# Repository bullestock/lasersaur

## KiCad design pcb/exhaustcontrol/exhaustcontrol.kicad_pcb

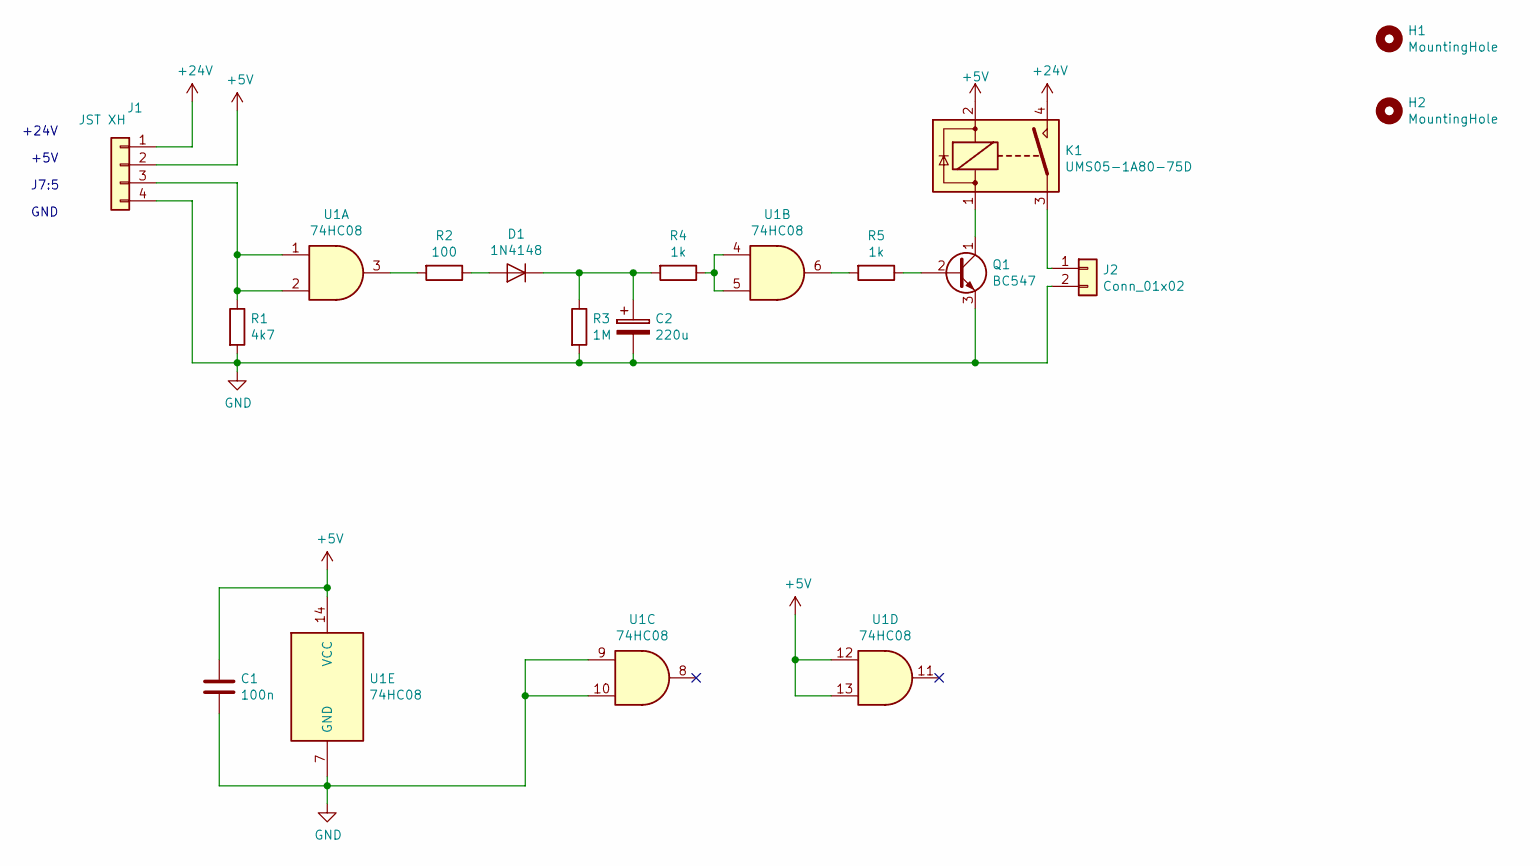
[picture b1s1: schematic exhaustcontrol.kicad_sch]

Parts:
C1: 100n; C_Axial_L5.1mm_D3.1mm_P10.00mm_Horizontal
C2: 220u; CP_Radial_D10.0mm_P2.50mm_P5.00mm
D1: 1N4148; D_DO-35_SOD27_P7.62mm_Horizontal
H1, H2: MountingHole; MountingHole_3.2mm_M3
J1: JST XH; JST_XH_B04B-XH-A_1x04_P2.50mm_Vertical
J2: Conn_01x02; JST_XH_B02B-XH-A_1x02_P2.50mm_Vertical
K1: UMS05-1A80-75D; DIL-relay
Q1: BC547; TO-92_Wide
R1: 4k7; R_Axial_DIN0411_L9.9mm_D3.6mm_P12.70mm_Horizontal
R2: 100; R_Axial_DIN0411_L9.9mm_D3.6mm_P12.70mm_Horizontal
R3: 1M; R_Axial_DIN0411_L9.9mm_D3.6mm_P12.70mm_Horizontal
R4, R5: 1k; R_Axial_DIN0411_L9.9mm_D3.6mm_P12.70mm_Horizontal
U1: 74HC08; DIP-14_W7.62mm_LongPads

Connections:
+5V: C1.1, J1.2, K1.2, U1.12, U1.13, U1.14 (VCC)
+24V: J1.1, K1.4
GND: C1.2, C2.2, J1.4, J2.2, Q1.3 (E), R1.2, R3.2, U1.7 (GND), U1.9, U1.10
unnamed: C2.1, D1.1 (K), R3.1, R4.2
unnamed: D1.2 (A), R2.1
unnamed: J1.3, R1.1, U1.1, U1.2
unnamed: J2.1, K1.3
unnamed: K1.1, Q1.1 (C)
unnamed: Q1.2 (B), R5.1
unnamed: R2.2, U1.3
unnamed: R4.1, U1.4, U1.5
unnamed: R5.2, U1.6

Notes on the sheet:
+24V
+5V
J7:5
GND

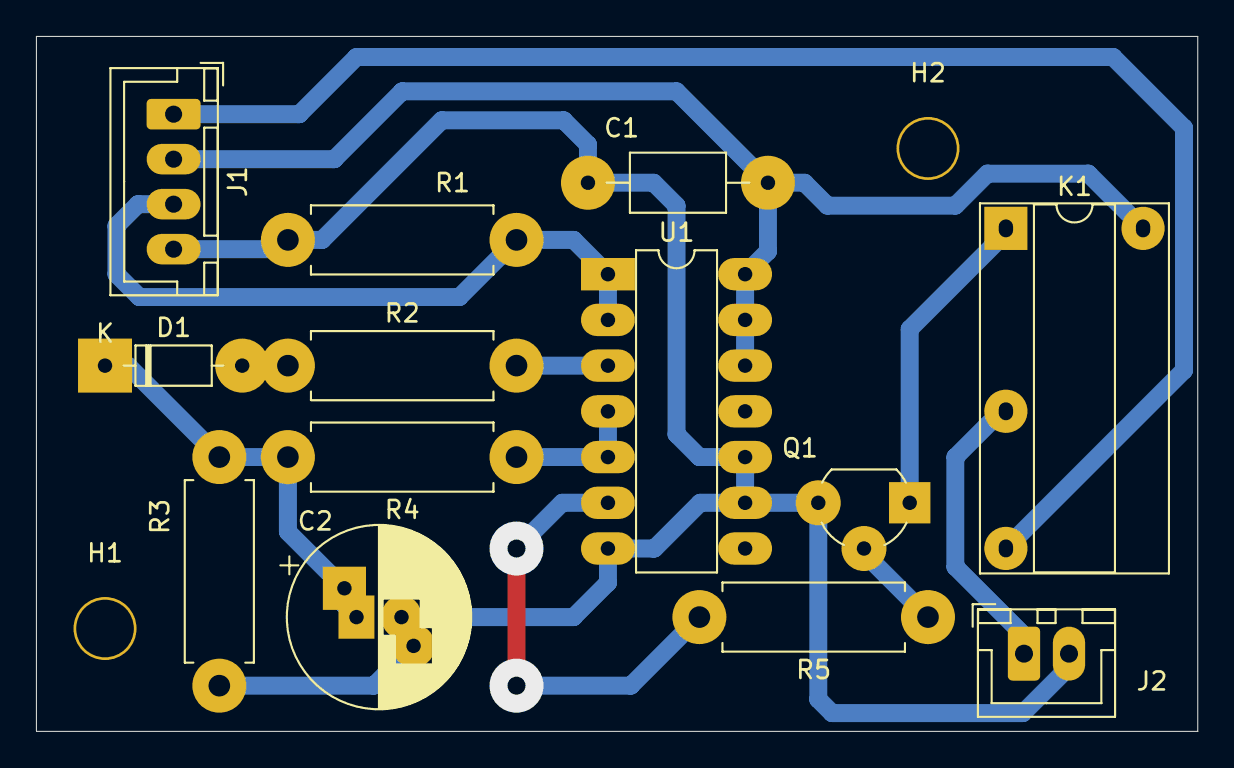
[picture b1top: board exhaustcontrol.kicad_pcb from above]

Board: 2 copper layers, 64.5 x 38.6 mm, 15 parts (0 on the bottom side), 12 nets.

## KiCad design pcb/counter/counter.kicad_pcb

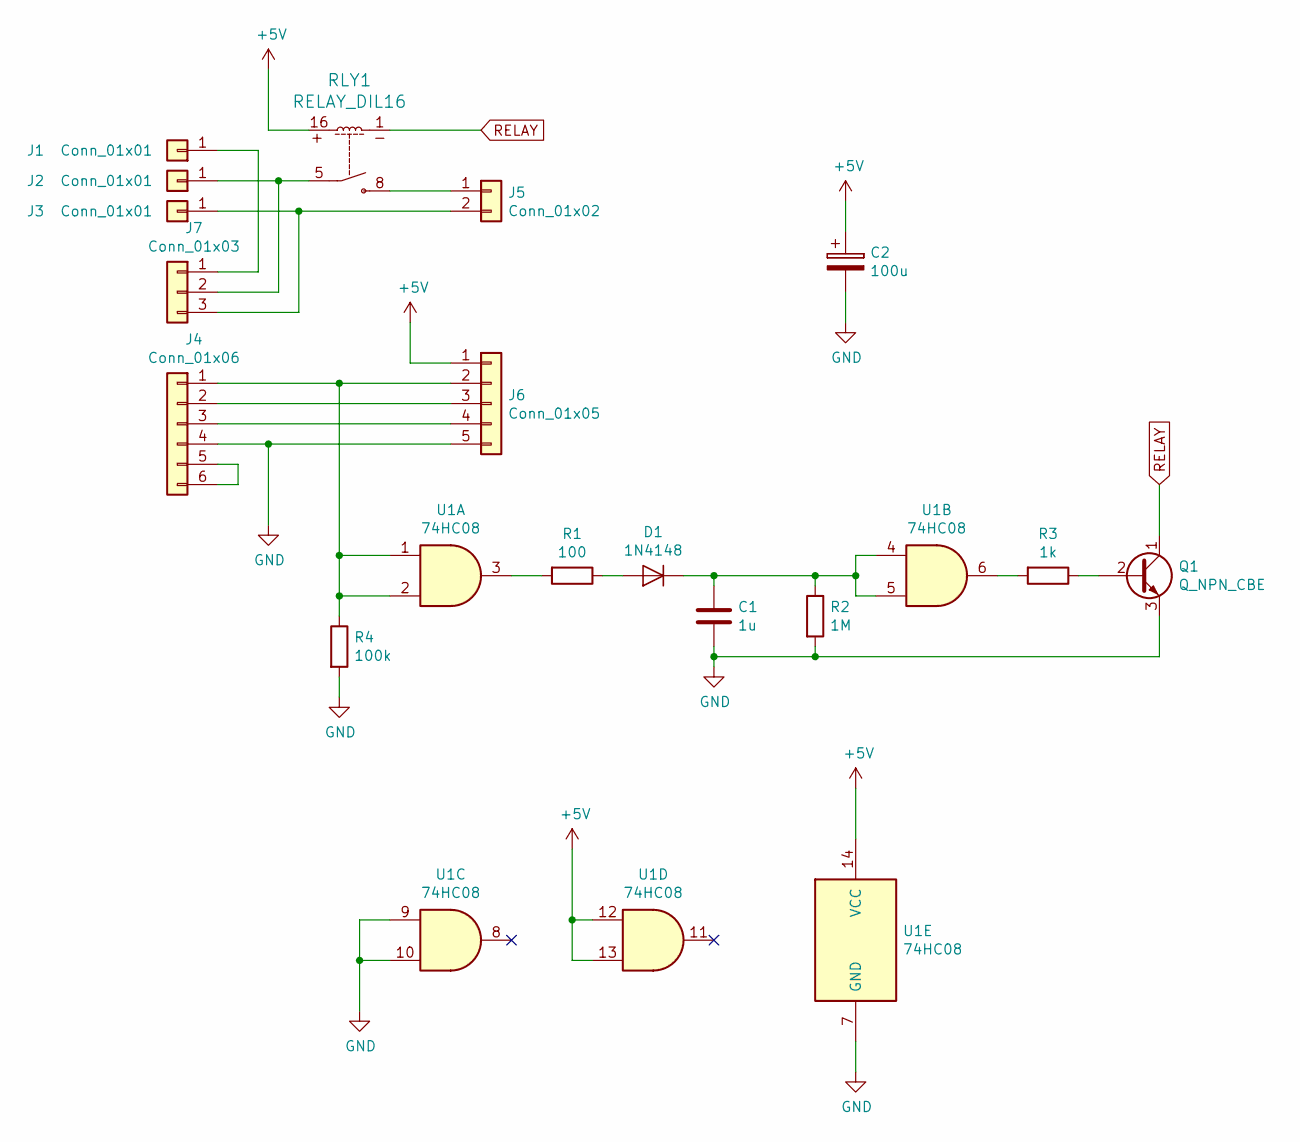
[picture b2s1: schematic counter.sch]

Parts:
C1: 1u; C_Rect_L11.0mm_W7.3mm_P10.00mm_MKT
C2: 100u; CP_Radial_D10.0mm_P2.50mm_P5.00mm
D1: 1N4148; D_DO-41_SOD81_P10.16mm_Horizontal
J1, J2, J3: Conn_01x01; Pin_D1.0mm_L10.0mm
J4: Conn_01x06; TerminalBlock_bornier-6_P5.08mm
J5: Conn_01x02; TerminalBlock_bornier-2_P5.08mm
J6: Conn_01x05; JST_XH_B05B-XH-A_1x05_P2.50mm_Vertical
J7: Conn_01x03; TerminalBlock_Altech_AK300-3_P5.00mm
Q1: Q_NPN_CBE; TO-92L_Wide
R1: 100; R_Axial_DIN0411_L9.9mm_D3.6mm_P12.70mm_Horizontal
R2: 1M; R_Axial_DIN0411_L9.9mm_D3.6mm_P5.08mm_Vertical
R3: 1k; R_Axial_DIN0411_L9.9mm_D3.6mm_P12.70mm_Horizontal
R4: 100k; R_Axial_DIN0411_L9.9mm_D3.6mm_P7.62mm_Vertical
RLY1: RELAY_DIL16; DIP-16_Relay
U1: 74HC08; DIP-14_W7.62mm_LongPads

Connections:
+5V: C2.1, J6.1, RLY1.16, U1.12, U1.13, U1.14 (VCC)
GND: C1.2, C2.2, J4.4, J6.5, Q1.3 (E), R2.2, R4.2, U1.7 (GND), U1.9, U1.10
unnamed: C1.1, D1.1 (K), R2.1, U1.4, U1.5
unnamed: D1.2 (A), R1.1
unnamed: J1.1, J7.1
unnamed: J2.1, J7.2, RLY1.5
unnamed: J3.1, J5.2, J7.3
unnamed: J4.1, J6.2, R4.1, U1.1, U1.2
unnamed: J4.2, J6.3
unnamed: J4.3, J6.4
unnamed: J4.5, J4.6
unnamed: J5.1, RLY1.8
unnamed: Q1.2 (B), R3.1
unnamed: R1.2, U1.3
unnamed: R3.2, U1.6
RELAY: Q1.1 (C), RLY1.1

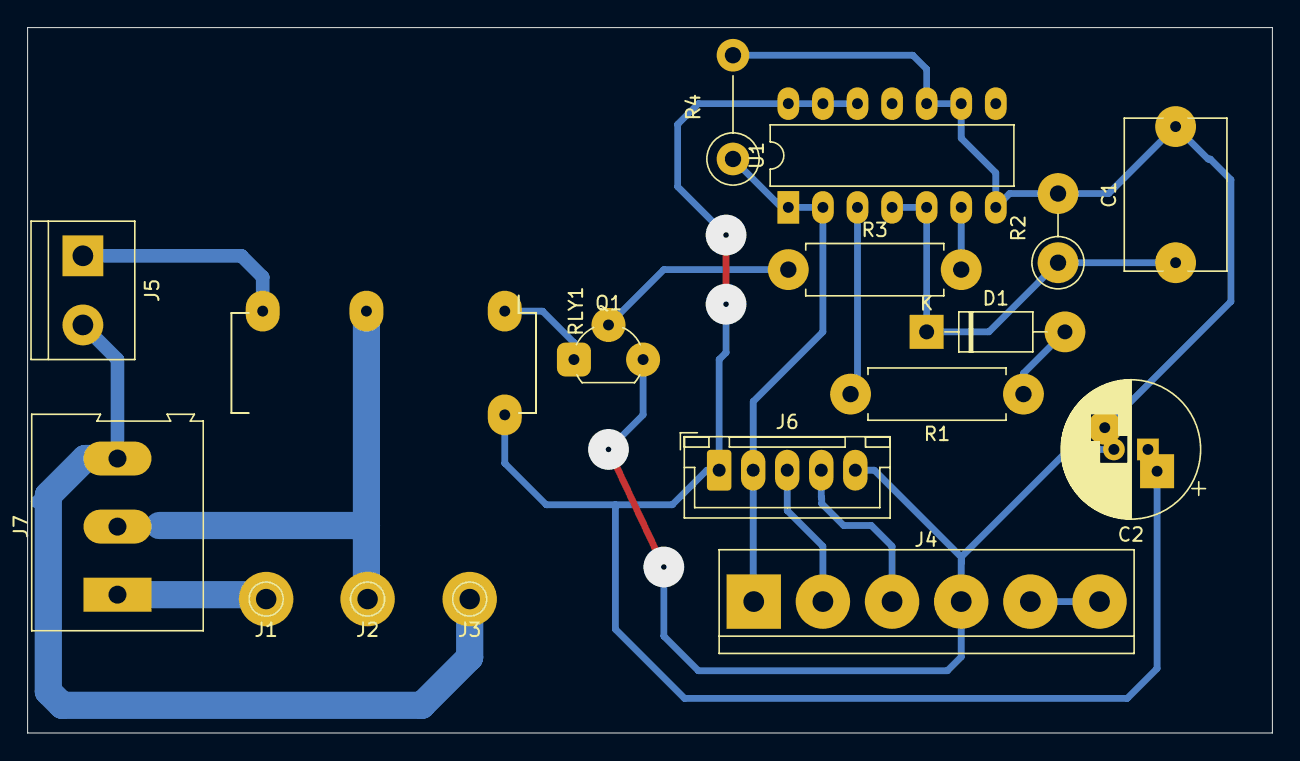
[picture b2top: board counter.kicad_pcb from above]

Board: 2 copper layers, 91.4 x 51.8 mm, 17 parts (0 on the bottom side), 16 nets.

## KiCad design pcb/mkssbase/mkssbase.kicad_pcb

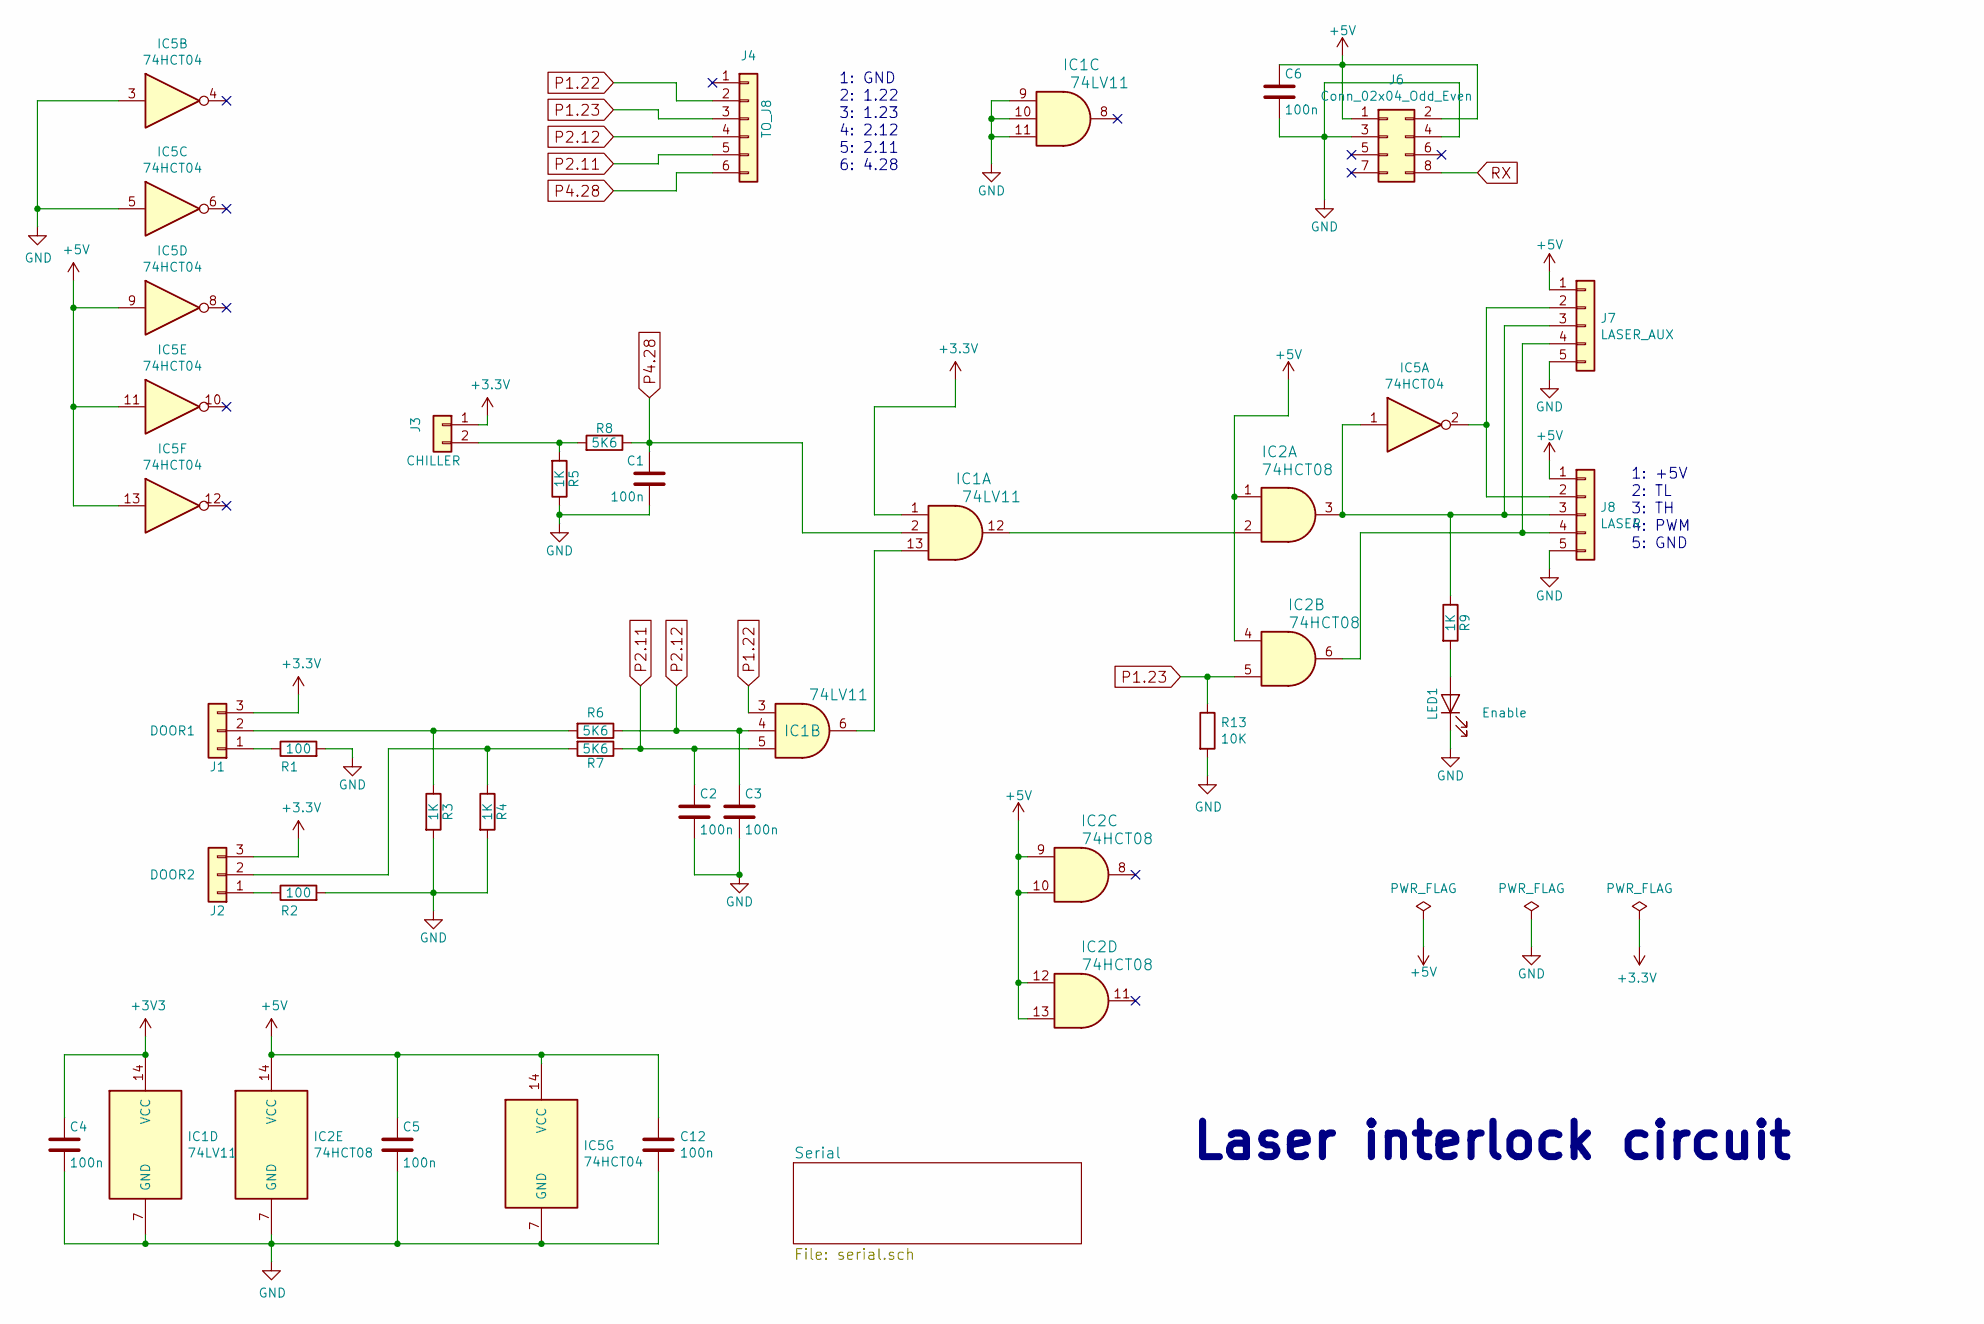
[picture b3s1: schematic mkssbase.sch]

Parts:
C1, C2, C3, C4, C5, C6, C12: 100n; C_0603_1608Metric
IC1: 74LV11; SOIC-14_3.9x8.7mm_P1.27mm
IC2: 74HCT08; SOIC-14_3.9x8.7mm_P1.27mm
IC5: 74HCT04; SOIC-14_3.9x8.7mm_P1.27mm
J1: DOOR1; JST_PH_B3B-PH-K_1x03_P2.00mm_Vertical
J2: DOOR2; JST_PH_B3B-PH-K_1x03_P2.00mm_Vertical
J3: CHILLER; JST_PH_B2B-PH-K_1x02_P2.00mm_Vertical
J4: TO_J8; JST_XH_B06B-XH-A_1x06_P2.50mm_Vertical
J6: Conn_02x04_Odd_Even; PinSocket_2x04_P2.54mm_Vertical
J7: LASER_AUX; JST_PH_B5B-PH-K_1x05_P2.00mm_Vertical
J8: LASER; JST_PH_B5B-PH-K_1x05_P2.00mm_Vertical
LED1: Enable; LED_0603_1608Metric
R1, R2: 100; R_0603_1608Metric
R3, R4, R5, R9: 1K; R_0603_1608Metric
R6, R7, R8: 5K6; R_0603_1608Metric
R13: 10K; R_0603_1608Metric

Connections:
+5V: C5.1, C6.1, C12.1, IC2.1, IC2.4, IC2.9, IC2.10, IC2.12, IC2.13, IC2.14 (VCC), IC5.9, IC5.11, IC5.13, IC5.14 (VCC), J6.1, J6.2, J7.1, J8.1; also elsewhere on the board
GND: C1.2, C2.2, C3.2, C4.2, C5.2, C6.2, C12.2, IC1.7 (GND), IC1.9, IC1.10, IC1.11, IC2.7 (GND), IC5.3, IC5.5, IC5.7 (GND), J6.3, J6.4, J7.5, J8.5, LED1.1 (K), R1.2, R2.2, R3.2, R4.2, R5.1, R13.2; also elsewhere on the board
unnamed: IC1.12, IC2.2
unnamed: IC1.6, IC1.13
unnamed: IC2.3, IC5.1, J7.3, J8.3, R9.1
unnamed: IC2.6, J7.4, J8.4
unnamed: IC5.2, J7.2, J8.2
unnamed: J1.1, R1.1
unnamed: J1.2, R3.1, R6.2
unnamed: J2.1, R2.1
unnamed: J2.2, R4.1, R7.2
unnamed: J3.2, R5.2, R8.2
unnamed: LED1.2 (A), R9.2
P1.22: IC1.3, J4.2
P1.23: IC2.5, J4.3, R13.1
P2.11: C2.1, IC1.5, J4.5, R7.1
P2.12: C3.1, IC1.4, J4.4, R6.1
P4.28: C1.1, IC1.2, J4.6, R8.1
RX: J6.8; also elsewhere on the board

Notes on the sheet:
1: +5V 2: TL 3: TH 4: PWM 5: GND
Laser interlock circuit
1: GND 2: 1.22 3: 1.23 4: 2.12 5: 2.11 6: 4.28

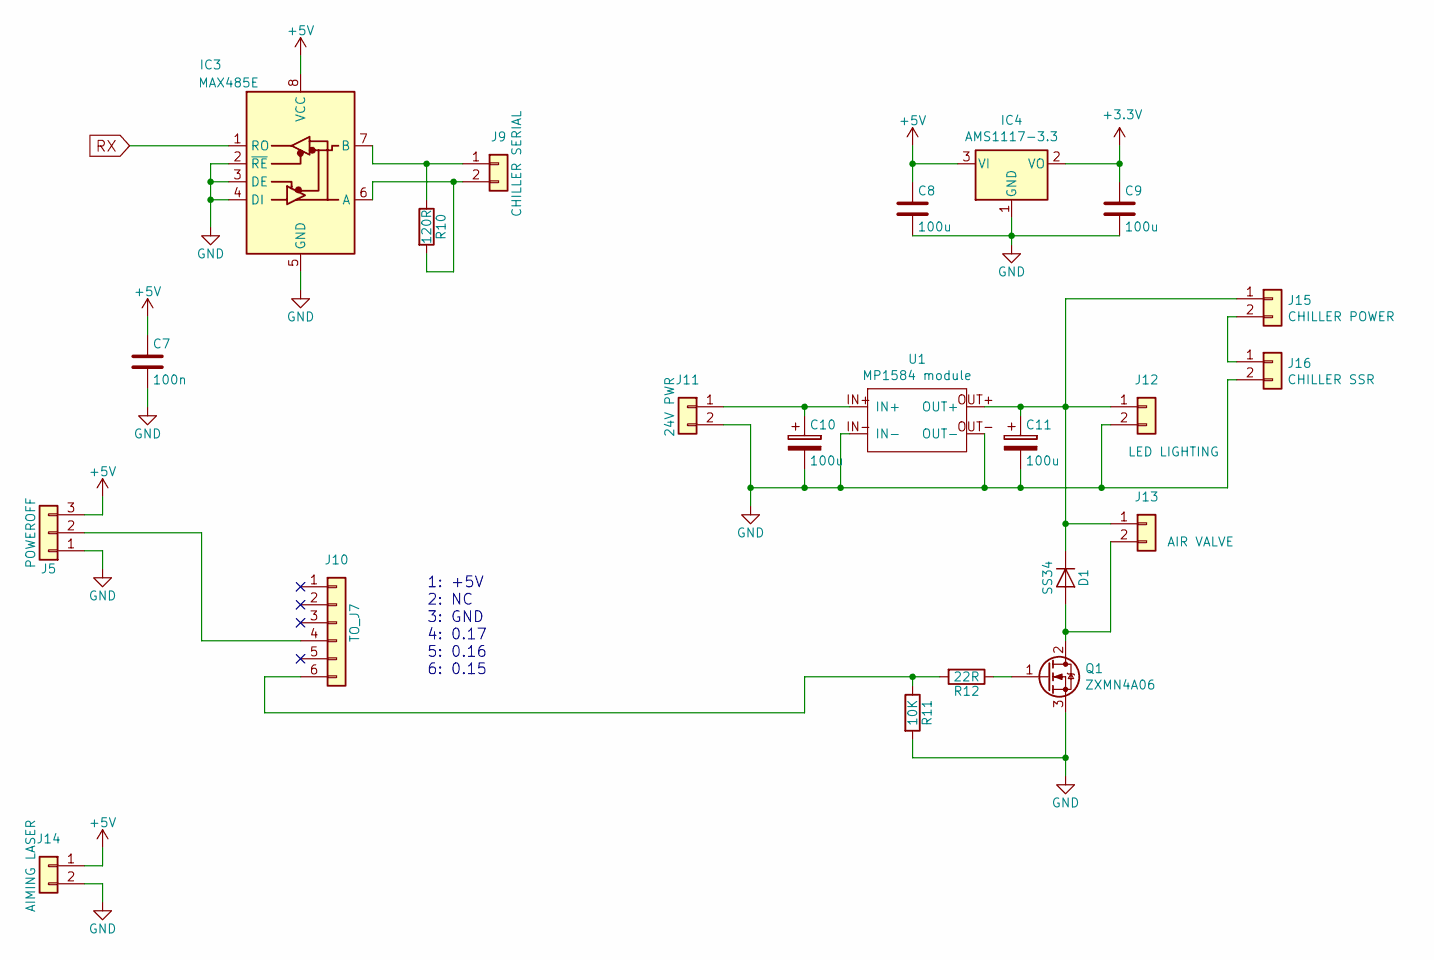
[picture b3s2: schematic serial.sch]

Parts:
C7: 100n; C_0603_1608Metric
C8, C9, C10, C11: 100u; CP_Elec_10x10
D1: SS34; D_SMA
IC3: MAX485E; SOIC-8_3.9x4.9mm_P1.27mm
IC4: AMS1117-3.3; SOT-223-3_TabPin2
J5: POWEROFF; JST_PH_B3B-PH-K_1x03_P2.00mm_Vertical
J9: CHILLER SERIAL; JST_PH_B2B-PH-K_1x02_P2.00mm_Vertical
J10: TO_J7; JST_XH_B06B-XH-A_1x06_P2.50mm_Vertical
J11: 24V PWR; JST_PH_B2B-PH-K_1x02_P2.00mm_Vertical
J12: LED LIGHTING; JST_PH_B2B-PH-K_1x02_P2.00mm_Vertical
J13: AIR VALVE; JST_PH_B2B-PH-K_1x02_P2.00mm_Vertical
J14: AIMING LASER; JST_PH_B2B-PH-K_1x02_P2.00mm_Vertical
J15: CHILLER POWER; JST_PH_B2B-PH-K_1x02_P2.00mm_Vertical
J16: CHILLER SSR; JST_PH_B2B-PH-K_1x02_P2.00mm_Vertical
Q1: ZXMN4A06; SOT-223-3_TabPin2
R10: 120R; R_0603_1608Metric
R11: 10K; R_0603_1608Metric
R12: 22R; R_0603_1608Metric
U1: MP1584 module; MP1584-module

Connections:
+5V: C7.1, C8.1, IC3.8 (VCC), IC4.3 (VI), J5.3, J14.1; also elsewhere on the board
GND: C7.2, C8.2, C9.2, C10.2, C11.2, IC3.2 (~RE), IC3.3 (DE), IC3.4 (DI), IC3.5 (GND), IC4.1 (GND), J5.1, J11.2, J12.2, J14.2, J16.2, Q1.3 (S), R11.2, U1.IN-, U1.OUT-; also elsewhere on the board
unnamed: C10.1, J11.1, U1.IN+
unnamed: C11.1, D1.1 (K), J12.1, J13.1, J15.1, U1.OUT+
unnamed: D1.2 (A), J13.2, Q1.2 (D)
unnamed: IC3.6 (A), J9.2, R10.2
unnamed: IC3.7 (B), J9.1, R10.1
unnamed: J5.2, J10.4
unnamed: J10.6, R11.1, R12.2
unnamed: J15.2, J16.1
unnamed: Q1.1 (G), R12.1
RX: IC3.1 (RO); also elsewhere on the board

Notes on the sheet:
1: +5V 2: NC 3: GND 4: 0.17 5: 0.16 6: 0.15

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
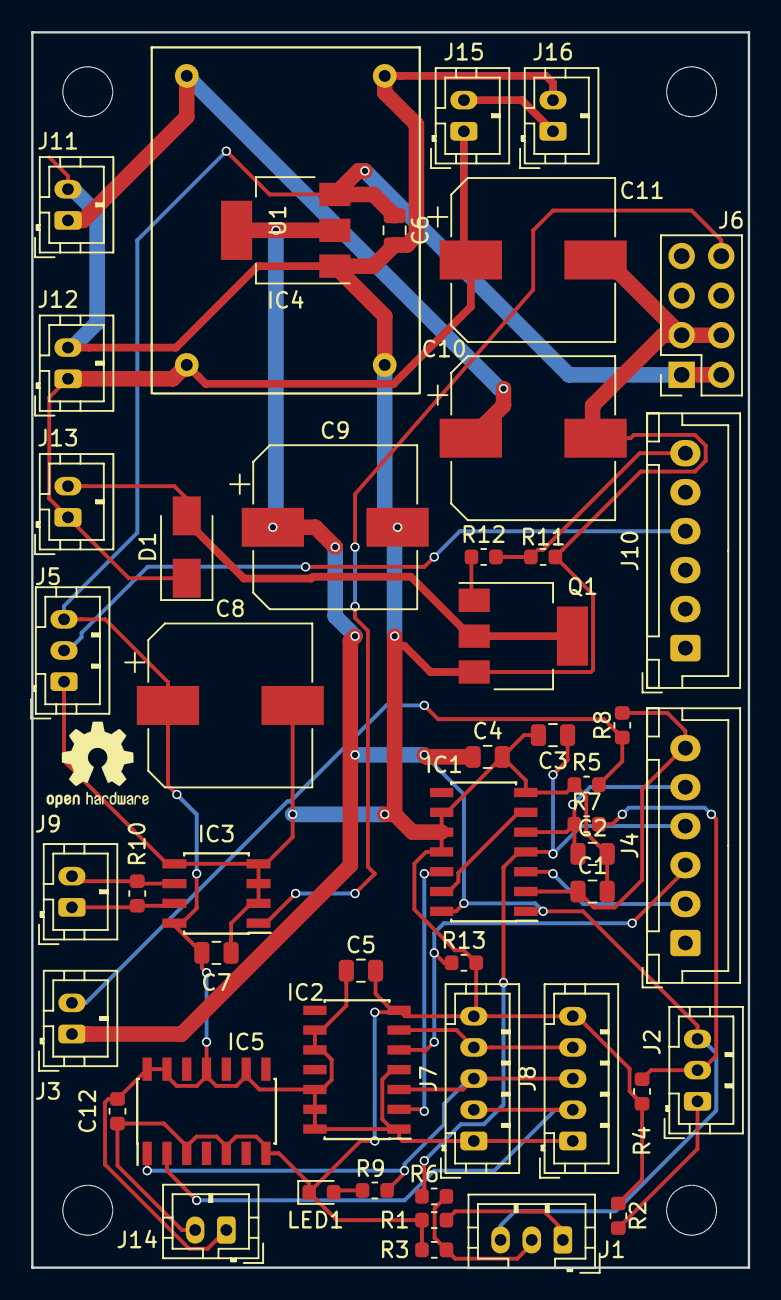
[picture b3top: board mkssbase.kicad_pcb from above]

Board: 2 copper layers, 46.0 x 79.2 mm, 50 parts (0 on the bottom side), 29 nets.

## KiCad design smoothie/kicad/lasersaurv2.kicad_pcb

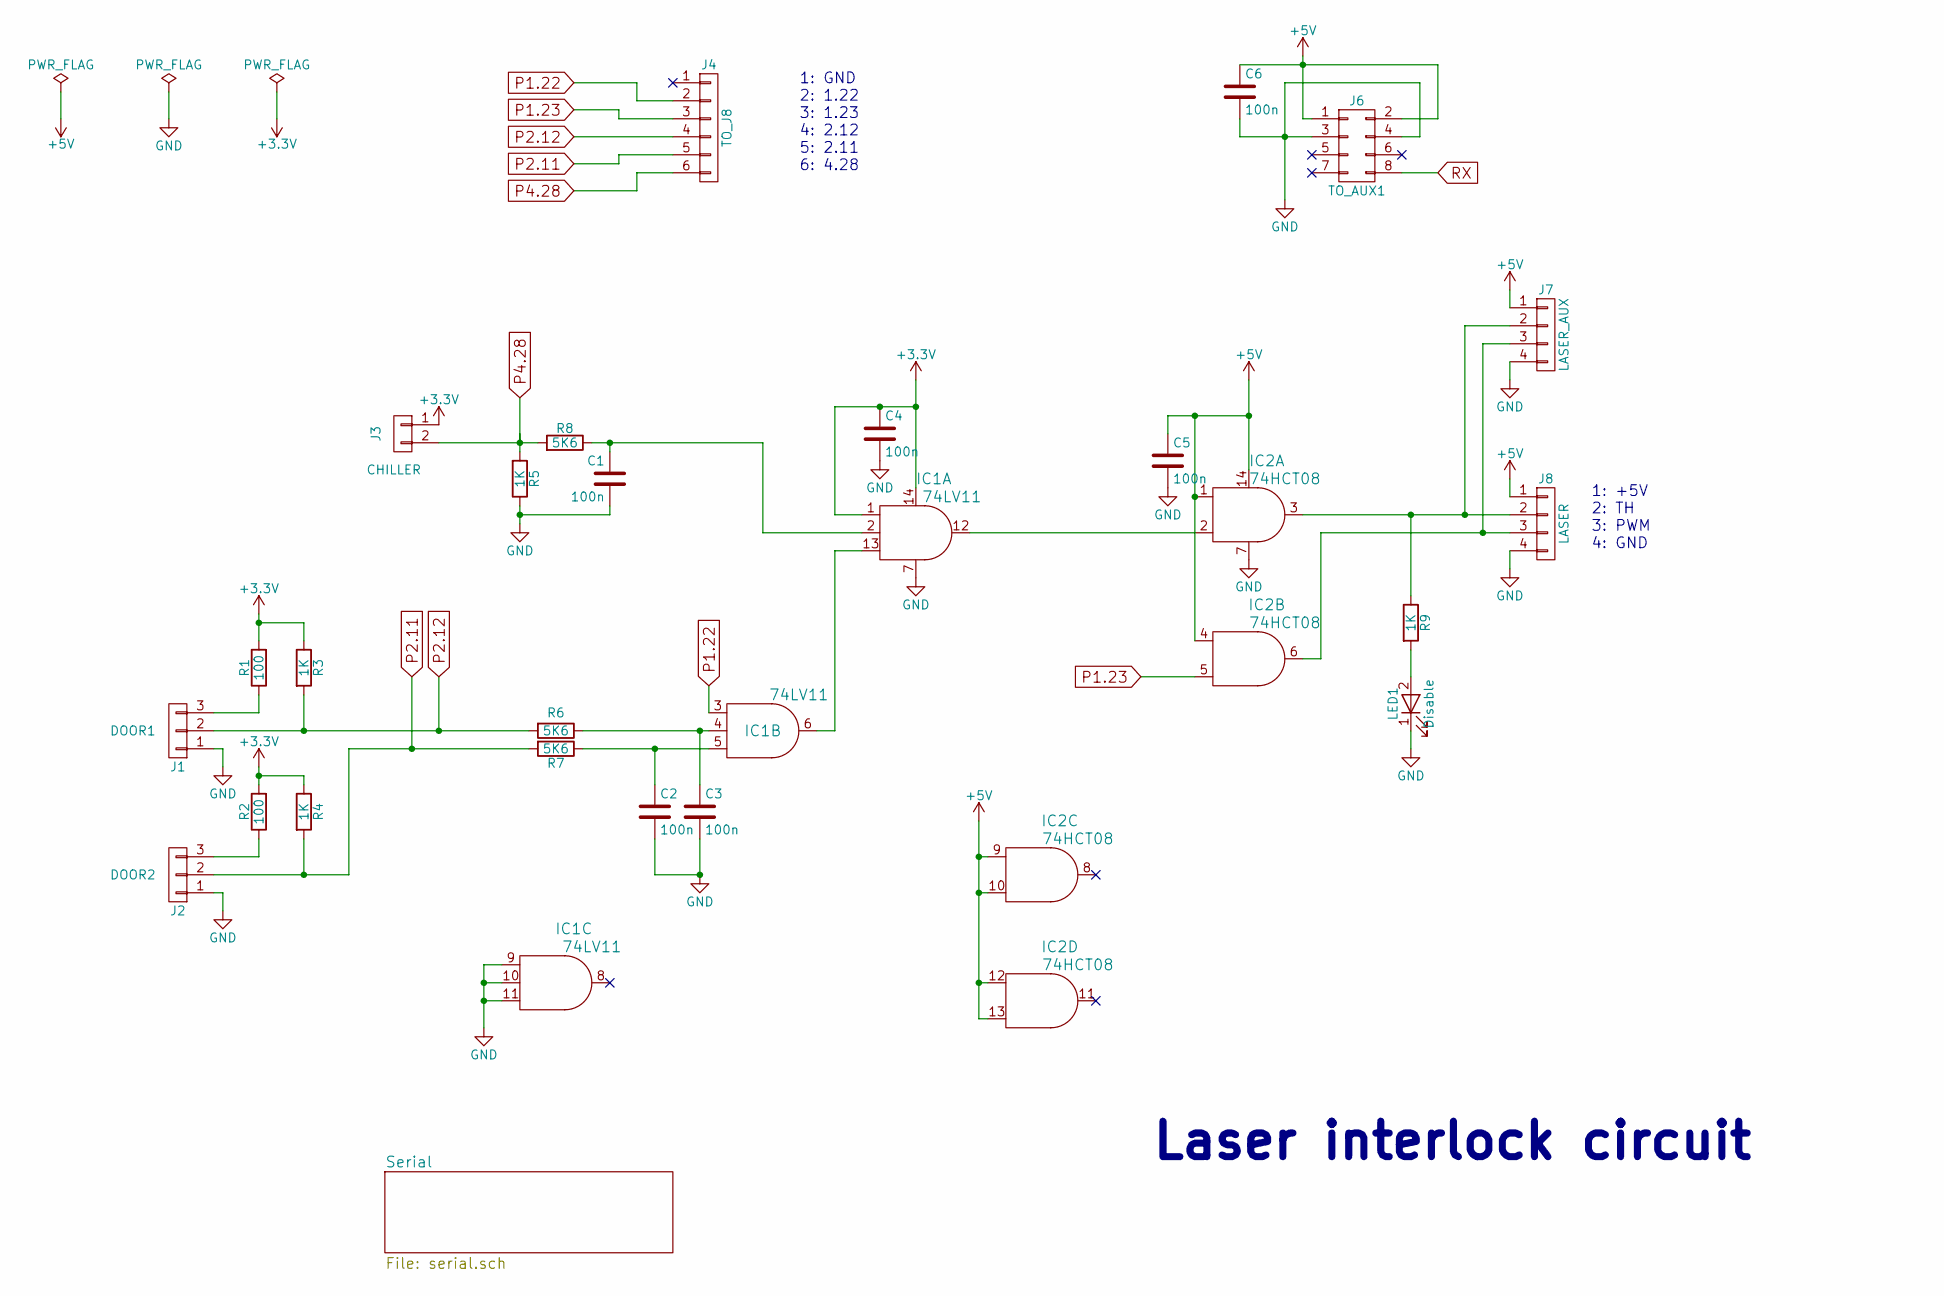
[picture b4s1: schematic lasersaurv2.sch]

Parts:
C1, C2, C3, C4, C5, C6: 100n; C_0805
IC1: 74LV11; SOIC-14_N
IC2: 74HCT08; SOIC-14_N
J1: DOOR1; JST_PH_B3B-PH-K_03x2.00mm_Straight
J2: DOOR2; JST_PH_B3B-PH-K_03x2.00mm_Straight
J3: CHILLER; JST_PH_B2B-PH-K_02x2.00mm_Straight
J4: TO_J8; PINHEAD1-6
J6: TO_AUX1; Pin_Header_Straight_2x04_Pitch2.54mm
J7: LASER_AUX; JST_PH_B4B-PH-K_04x2.00mm_Straight
J8: LASER; JST_PH_B4B-PH-K_04x2.00mm_Straight
LED1: Disable; LED_0603
R1, R2: 100; R_0603
R3, R4, R5, R9: 1K; R_0603
R6, R7, R8: 5K6; R_0603

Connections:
+3V3: C4.1, IC1.1 (1A), IC1.14 (VDD), J3.1, R1.2, R2.2, R3.1, R4.1; also elsewhere on the board
+5V: C5.1, C6.1, IC2.1 (1A), IC2.4 (2A), IC2.9 (3A), IC2.10 (3B), IC2.12 (4A), IC2.13 (4B), IC2.14 (VDD), J6.1, J6.2, J7.1, J8.1; also elsewhere on the board
GND: C1.2, C2.2, C3.2, C4.2, C5.2, C6.2, IC1.7 (VSS), IC1.9 (3A), IC1.10 (3B), IC1.11 (3C), IC2.7 (VSS), J1.1, J2.1, J6.3, J6.4, J7.4, J8.4, LED1.1 (K), R5.1; also elsewhere on the board
unnamed: C1.1, IC1.2 (1B), R8.1
unnamed: C2.1, IC1.5 (2C), R7.1
unnamed: C3.1, IC1.4 (2B), R6.1
unnamed: IC1.12 (1Y), IC2.2 (1B)
unnamed: IC1.6 (2Y), IC1.13 (1C)
unnamed: IC2.3 (1Y), J7.2, J8.2, R9.1
unnamed: IC2.6 (2Y), J7.3, J8.3
unnamed: J1.3, R1.1
unnamed: J2.3, R2.1
unnamed: LED1.2 (A), R9.2
P1.22: IC1.3 (2A), J4.2
P1.23: IC2.5 (2B), J4.3
P2.11: J2.2, J4.5, R4.2, R7.2
P2.12: J1.2, J4.4, R3.2, R6.2
P4.28: J3.2, J4.6, R5.2, R8.2
RX: J6.8; also elsewhere on the board

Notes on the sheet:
1: +5V 2: TH 3: PWM 4: GND
Laser interlock circuit
1: GND 2: 1.22 3: 1.23 4: 2.12 5: 2.11 6: 4.28

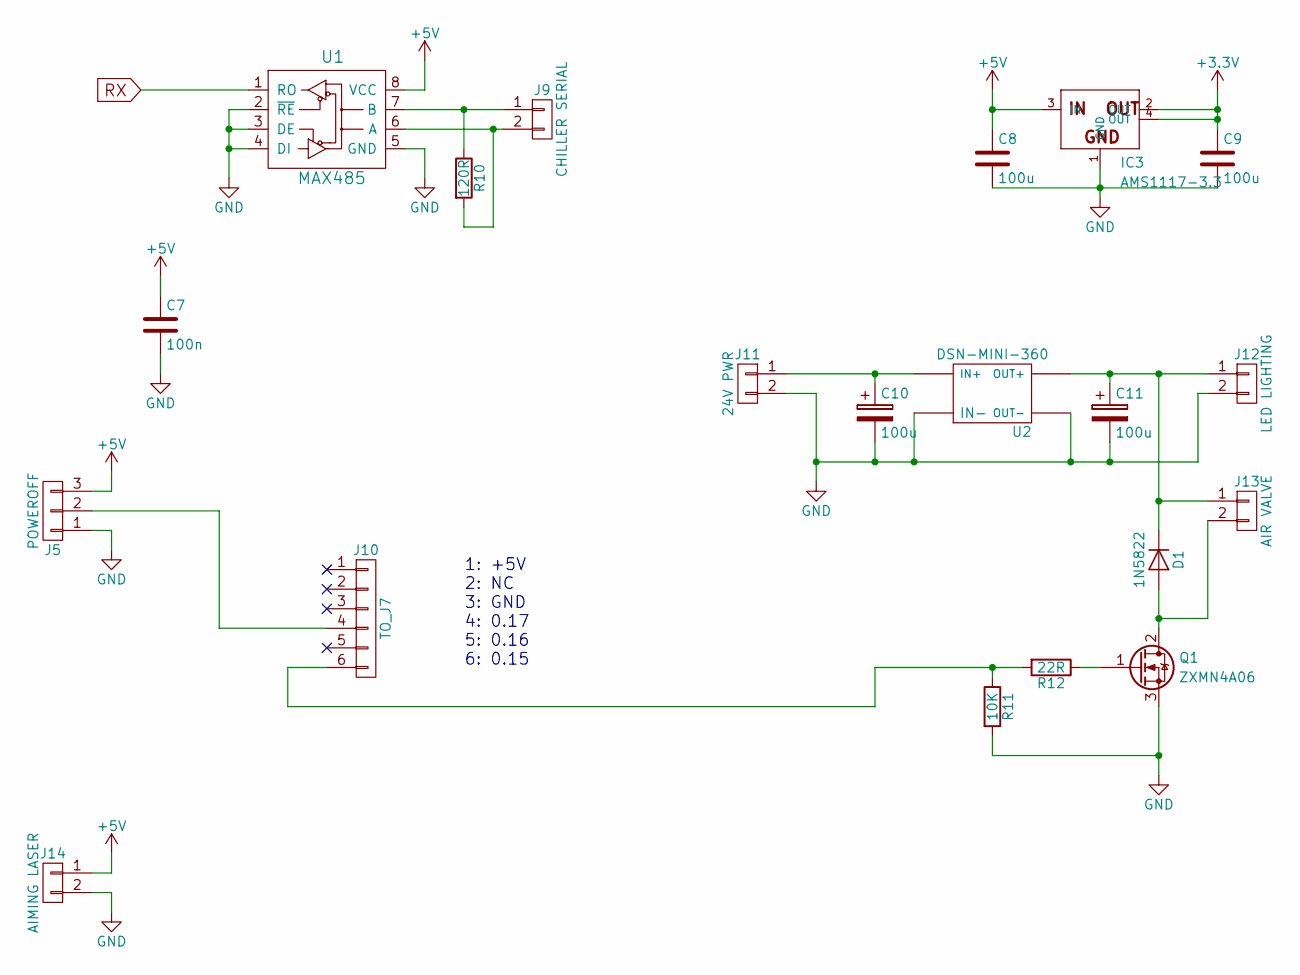
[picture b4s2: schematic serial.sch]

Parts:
C7: 100n; C_0805
C8, C9, C10, C11: 100u; SMD-1206_Pol
D1: 1N5822; D_SMC_Standard
IC3: AMS1117-3.3; SOT-223
J5: POWEROFF; JST_PH_B3B-PH-K_03x2.00mm_Straight
J9: CHILLER SERIAL; JST_PH_B2B-PH-K_02x2.00mm_Straight
J10: TO_J7; PINHEAD1-6
J11: 24V PWR; JST_PH_B2B-PH-K_02x2.00mm_Straight
J12: LED LIGHTING; JST_PH_B2B-PH-K_02x2.00mm_Straight
J13: AIR VALVE; JST_PH_B2B-PH-K_02x2.00mm_Straight
J14: AIMING LASER; JST_PH_B2B-PH-K_02x2.00mm_Straight
Q1: ZXMN4A06; SOT-223-3Lead_TabPin2
R10: 120R; R_0603
R11: 10K; R_0603
R12: 22R; R_0603
U1: MAX485; SOIC-8-N
U2: DSN-MINI-360

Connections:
+3V3: C9.1, IC3.2 (OUT), IC3.4 (OUT); also elsewhere on the board
+5V: C7.1, C8.1, IC3.3 (IN), J5.3, J14.1, U1.8 (VCC); also elsewhere on the board
GND: C7.2, C8.2, C9.2, C10.2, C11.2, IC3.1 (GND), J5.1, J11.2, J12.2, J14.2, Q1.3 (S), R11.2, U1.2 (~RE), U1.3 (DE), U1.4 (DI), U1.5 (GND), U2.IN-, U2.OUT-; also elsewhere on the board
unnamed: C10.1, J11.1, U2.IN+
unnamed: C11.1, D1.1 (K), J12.1, J13.1, U2.OUT+
unnamed: D1.2 (A), J13.2, Q1.2 (D)
unnamed: J9.1, R10.1, U1.7 (B)
unnamed: J9.2, R10.2, U1.6 (A)
unnamed: J5.2, J10.4
unnamed: J10.6, R11.1, R12.2
unnamed: Q1.1 (G), R12.1
RX: U1.1 (RO); also elsewhere on the board

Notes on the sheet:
1: +5V 2: NC 3: GND 4: 0.17 5: 0.16 6: 0.15

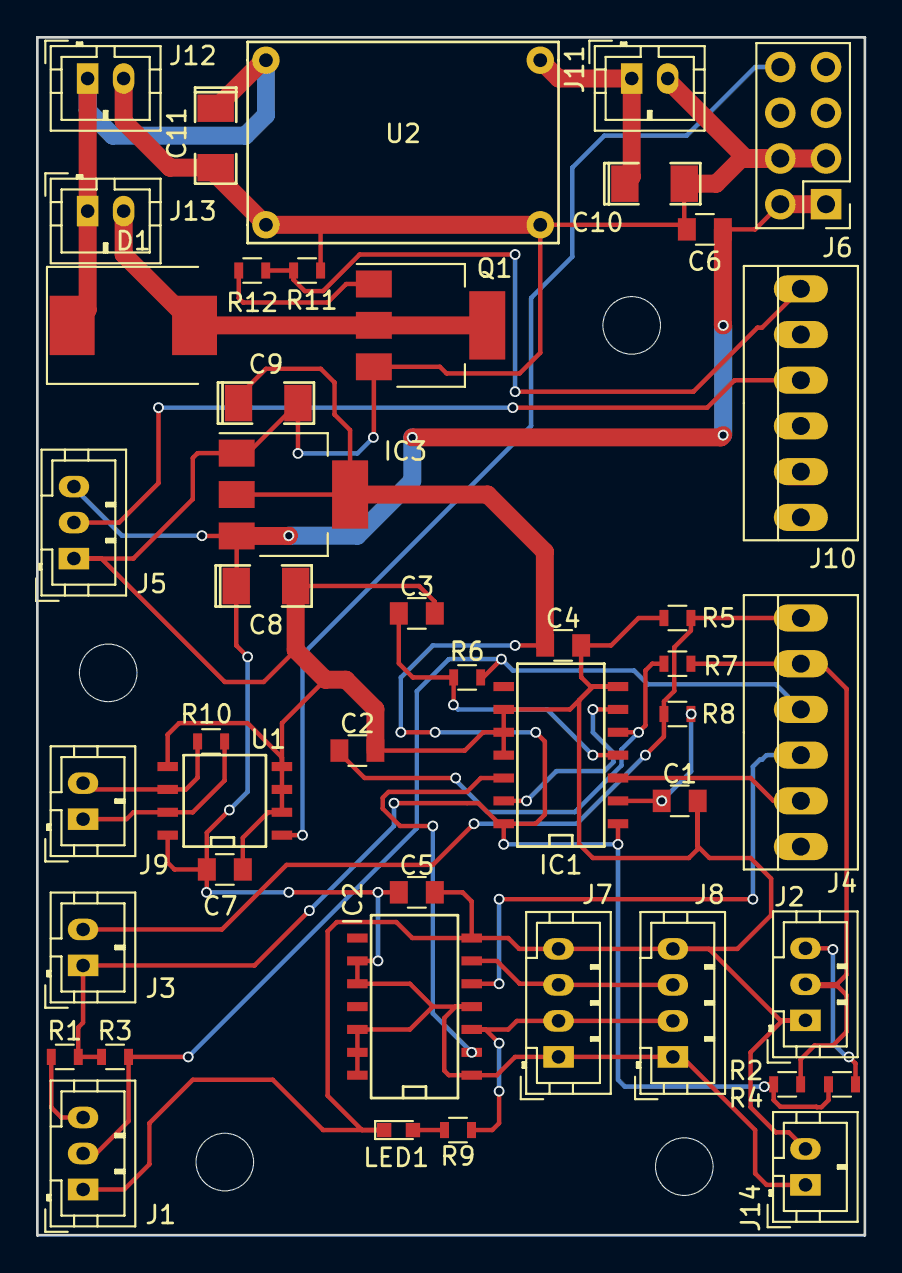
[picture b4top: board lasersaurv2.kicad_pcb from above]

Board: 2 copper layers, 46.0 x 66.5 mm, 45 parts (0 on the bottom side), 27 nets.
